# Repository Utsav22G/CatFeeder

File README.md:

# CatFeeder
Final Project for Real World Microcontrollers Fall 2020 - Kitty Caddy cat feeder 

## Acknowledgement
Stan Reifel

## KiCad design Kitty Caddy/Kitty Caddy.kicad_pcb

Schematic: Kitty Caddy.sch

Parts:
C1: 10uF; CP_Radial_D5.0mm_P2.00mm
C2, C7, C8, C9, C10, C13, C14, C15: 0.1uF; C_0603
C3: 100uF; CP_Radial_D10.0mm_P5.00mm
C4: 47uF; CP_Radial_D10.0mm_P5.00mm
C5: 0.01uF; C_0603
C6: 220uF; CP_Radial_D12.5mm_P5.00mm
C11, C12: 22pF; C_0603
D1: B340; D_SMA
D2: RX Red; LED_0603
D3: TX Green; LED_0603
D4: D_RESET; D_SMA
D5: Debug LED; LED_0603
J1: PJ-051A; CUI_PJ-051A
J2: Motor Conn VM; Pin_Header_Straight_1x04_Pitch2.54mm
J3: Optocoupler Conn VM; Pin_Header_Straight_1x05_Pitch2.54mm
J4: Serial Conn RM; Pin_Header_Straight_1x06_Pitch2.54mm
J5: ICSP Header VM; Pin_Header_Straight_2x03_Pitch2.54mm
L1: 15uH; L_Radial_D12.0mm_P10.00mm_Neosid_SD12_style1
R1, R2, R8, R9, R12, R13, R14, R16, R17: 10k; R_0603
R3: 10k; R_0805
R4: 3.24k; R_0805
R5: 120; R_0603
R6: 22k; R_0603
R7, R10, R11, R15: 1k; R_0603
SW1: UP; SPST_ESwitch
SW2: DOWN; SPST_ESwitch
SW3: MODE; SPST_ESwitch
TP1: TP_RXL; TestPoint_Pad_D1.5mm
TP2: TP_TXL; TestPoint_Pad_D1.5mm
TP3: TP_UP1; TestPoint_Pad_D1.5mm
TP4: TP_UP2; TestPoint_Pad_D1.5mm
TP5: TP_X1; TestPoint_Pad_D1.5mm
TP6: TP_X2; TestPoint_Pad_D1.5mm
U1: OLED_Display; Pin_Header_Straight_1x04_Pitch2.54mm
U2: DRV8825
U3: TPS5430DDA; TI_SO-PowerPAD-8_ThermalVias
U4: DS3231 RTC; Pin_Header_Straight_1x08_Pitch2.54mm
U5: 74HC14D; SOIC-14_N
U6: ATmega328P-AU; TQFP-32_7x7mm_Pitch0.8mm
Y1: 16MHz; SMD-3225_4P

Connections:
+5V: C6.1, C7.1, C14.2, D4.1 (K), J4.4, J5.2, L1.2, R1.2, R2.2, R3.1, R5.1, R6.2, R8.2, R9.2, R10.1, R11.1, R12.2, R17.2, U1.2, U2.5, U2.6, U4.1, U5.14, U6.4 (VCC), U6.6 (VCC), U6.18 (AVCC)
+12V: C1.1, C2.1, C3.1, C4.1, J1.1, U2.9, U3.7 (VIN)
DIR: U2.8, U6.14 (PB2)
DOWN_BTN: U5.6, U6.11 (PD7)
DTR: C8.2, J4.1, R7.2
GND: C1.2, C2.2, C3.2, C4.2, C6.2, C7.2, C9.2, C10.2, C11.2, C12.2, C13.2, C14.1, C15.2, D1.2 (A), D5.1 (K), J1.2, J1.3, J1.5, J1.6, J3.2, J3.4, J4.5, J4.6, J5.6, R4.2, R7.1, SW1.1, SW1.2, SW2.1, SW2.2, SW3.3, SW3.4, U1.1, U2.10, U2.16, U3.6 (GND), U3.9 (GNDPAD), U4.2, U5.7, U6.3 (GND), U6.5 (GND), U6.21 (GND), Y1.2, Y1.4
M0: U2.2, U6.32 (PD2)
M1: U2.3, U6.1 (PD3)
M2: U2.4, U6.2 (PD4)
MISO: J5.1, U6.16 (PB4)
MODE_BTN: U5.12, U6.10 (PD6)
MOSI: J5.4, U6.15 (PB3)
unnamed: C5.1, D1.1 (K), L1.1, U3.8 (PH)
unnamed: C5.2, U3.1 (BOOT)
unnamed: C9.1, R13.2, TP3.1, U5.1
unnamed: C10.1, R14.2, U5.5
unnamed: C11.1, TP5.1, U6.7 (XTAL1/PB6), Y1.1
unnamed: C12.1, TP6.1, U6.8 (XTAL2/PB7), Y1.3
unnamed: C13.1, R16.1, U5.13
unnamed: C15.1, U6.20 (AREF)
unnamed: D2.2 (A), R10.2, TP1.1
unnamed: D3.2 (A), R11.2, TP2.1
unnamed: D5.2 (A), R15.2
unnamed: J2.1, U2.13
unnamed: J2.2, U2.14
unnamed: J2.3, U2.12
unnamed: J2.4, U2.11
unnamed: J3.1, R5.2
unnamed: R8.1, R13.1, SW1.3, SW1.4
unnamed: R9.1, R14.1, SW2.3, SW2.4
unnamed: R16.2, R17.1, SW3.1, SW3.2
RESET_PIN: C8.1, D4.2 (A), J5.5, R12.1, U6.29 (~RESET~/PC6)
RXI: D2.1 (K), J4.2, U6.31 (PD1)
SCK: J5.3, R15.1, U6.17 (PB5)
SCL: R1.1, U1.3, U4.3, U6.28 (PC5)
SDA: R2.1, U1.4, U4.4, U6.27 (PC4)
SENSE: J3.5, R6.1, U6.23 (PC0)
STEP: U2.7, U6.13 (PB1)
TXO: D3.1 (K), J4.3, U6.30 (PD0)
UP_BTN: TP4.1, U5.2, U6.9 (PD5)
V_SNS: R3.2, R4.1, U3.4 (VSENSE)

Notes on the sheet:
VIN -> 10.8 V - 19.8 V
Buck Converter
Crystal Oscillator
Motor Driver
Serial TX and RX LEDs
SCK = PIN13
Hardware Debounce for buttons using a Schmitt-trigger IC https://hackaday.com/2015/12/09/embed-with-elliot-debounce-your-noisy-buttons-part-i/
Optocoupler
LED _AN = 1
Power Flags
User Input Buttons
Phototransistor Design Guide https://www.onsemi.com/pub/Collateral/AN-3005-D.PDF
Orange
Green
Blue
White
LED_CAT = 2
BJT_EMTR = 5
BJT_CLCTR = 4
Modules
I2C Pullup
Reset Pins

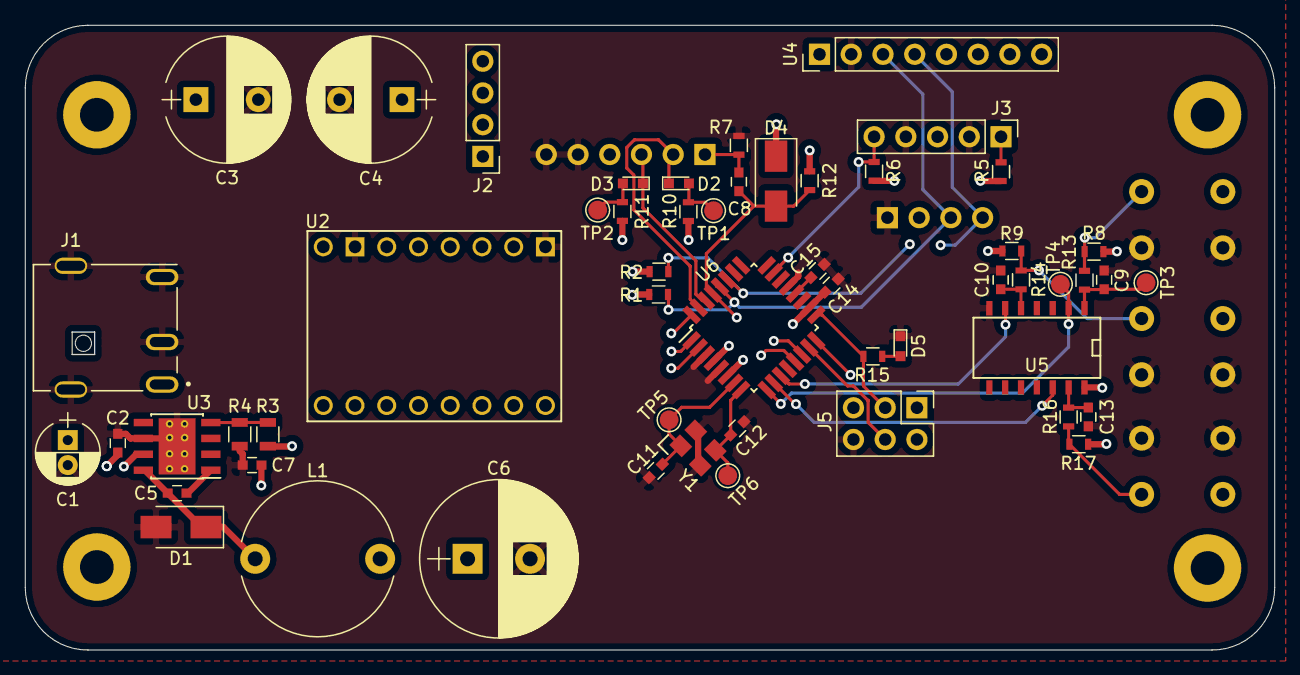
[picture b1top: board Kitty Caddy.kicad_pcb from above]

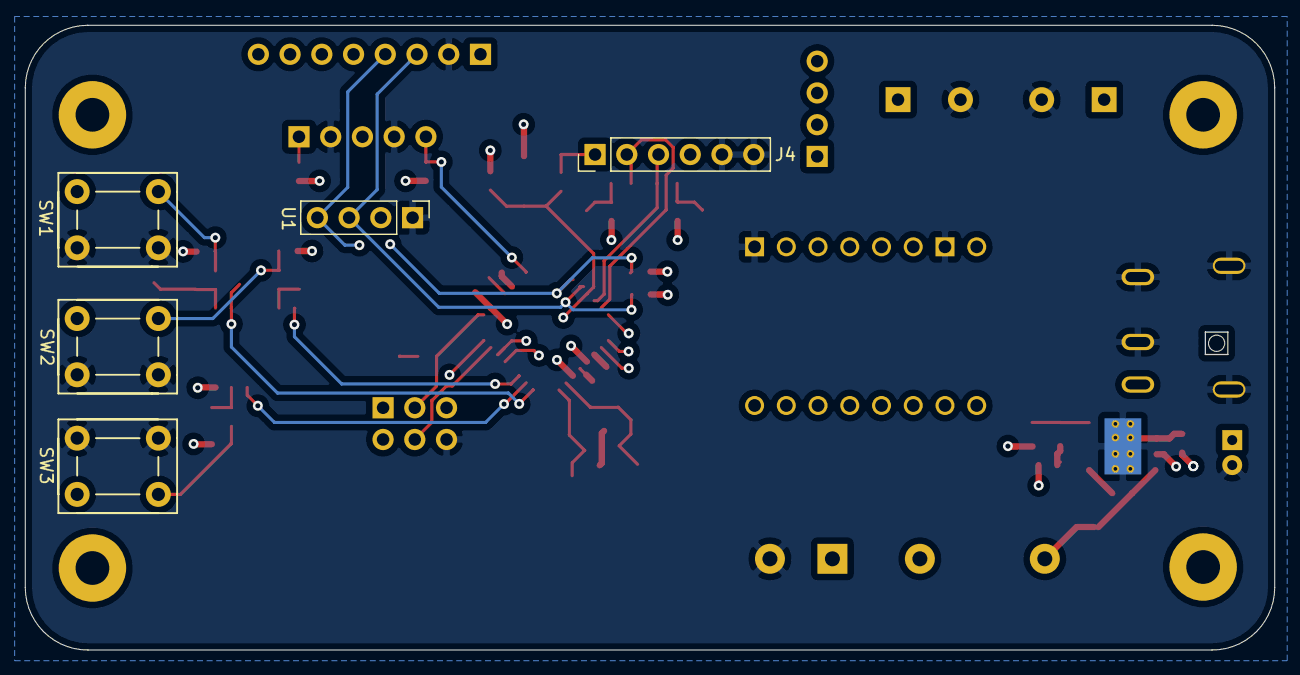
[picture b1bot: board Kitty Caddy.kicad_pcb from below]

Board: 4 copper layers, 100.0 x 50.0 mm, 59 parts (5 on the bottom side), 41 nets.

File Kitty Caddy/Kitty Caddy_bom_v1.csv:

Component,Description,Part,References,Value,Footprint,Quantity Per PCB,Datasheet,Vendor,Vendor Part #,Manufacturer,Link,Comments
1,Unpolarized capacitor,C,C5,0.01uF,C_0603,1,~,,,,,
2,Unpolarized capacitor,C,C2 C7 C8 C9 C10 C13 C14 C15,0.1uF,C_0603,8,~,,,,,
3,Polarized capacitor,CP,C3,100uF,CP_Radial_D10.0mm_P5.00mm,1,https://www.nichicon.co.jp/english/products/pdfs/e-ukl.pdf,DigiKey,493-13402-ND,Nichicon,,
4,Polarized capacitor,CP,C1,10uF,CP_Radial_D5.0mm_P2.00mm,1,https://www.nichicon.co.jp/english/products/pdfs/e-ukl.pdf,DigiKey,UKL1H100KDDANA-ND,Nichicon,,
5,Polarized capacitor,CP,C6,220uF,CP_Radial_D12.5mm_P5.00mm,1,https://www.nichicon.co.jp/english/products/pdfs/e-ukl.pdf,DigiKey,493-14487-ND,Nichicon,,
6,"Unpolarized capacitor, small symbol",C_Small,C11 C12,22pF,C_0603,2,~,LCSC,C1653,Samsung Electro-Mechanics,,
7,Polarized capacitor,CP,C4,47uF,CP_Radial_D10.0mm_P5.00mm,1,https://www.nichicon.co.jp/english/products/pdfs/e-ukl.pdf,DigiKey,493-13402-ND,Nichicon,,
8,"20V 3A Schottky Barrier Rectifier Diode, SMC",B340,D1,B340,D_SMA,1,1903051003_MDD-Jiangsu-Yutai-Elec-SS14_C2480.pdf,LCSC,C2480,Microdiode Electronics,,
9,Diode,D,D4,D_RESET,D_SMA,1,https://datasheet.lcsc.com/szlcsc/MDD-Jiangsu-Yutai-Elec-M7-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,LCSC,C95872,Microdiode Electronics,,
10,Light emitting diode,LED,D5,Debug LED,LED_0603,1,Everlight-Elec-19-217-BHC-ZL1M2RY-3T_C72041.pdf,LCSC,C72041,Everlight Elec,,
11,Light emitting diode,LED,D2,RX Red,LED_0805,1,Foshan-NationStar-Optoelectronics-FC-2012HRK-620D_C84256.pdf,LCSC,C84256,Foshan NationStar Optoelectronics,,
12,Light emitting diode,LED,D3,TX Green,LED_0603,1,Everlight-Elec-19-217-GHC-YR1S2-3T_C72043.pdf,LCSC,C72043,Everlight Elec,,
13,"Generic connector, double row, 02x03, odd/even pin numbering scheme (row 1 odd numbers, row 2 even numbers), script generated (kicad-library-utils/schlib/autogen/connector/)",Conn_02x03_Odd_Even,J5,ICSP Header VM,Pin_Header_Straight_2x03_Pitch2.54mm,1,~,DigiKey,1849-PR20203VBDN-ND,METZ CONNECT USA Inc.,,
14,"Generic connector, single row, 01x04, script generated (kicad-library-utils/schlib/autogen/connector/)",Conn_01x04,J2,Motor Conn VM,Pin_Header_Straight_1x04_Pitch2.54mm,1,~,DigiKey,WM2702-ND,Molex,,
15,"Generic connector, single row, 01x05, script generated (kicad-library-utils/schlib/autogen/connector/)",Conn_01x05,J3,Optocoupler Conn VM,Pin_Header_Straight_1x05_Pitch2.54mm,1,~,DigiKey,WM2703-ND,Molex,,
16,"DC Power Jack Conn 2.0 mm Center Pin, 2.5 A, Right Angle, Through Hole, Shielded",PJ-051A,J1,PJ-051A,CUI_PJ-051A,1,https://www.cuidevices.com/product/resource/pj-051a.pdf,DigiKey,CP-051A-ND,CUI Inc.,https://www.digikey.com/product-detail/en/cui-inc/PJ-051A/CP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,https://electronics.stackexchange.com/questions/2381/deciphe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
17,"Generic connector, single row, 01x06, script generated (kicad-library-utils/schlib/autogen/connector/)",Conn_01x06,J4,Serial Conn RM,Pin_Header_Straight_1x06_Pitch2.54mm,1,~,DigiKey,1849-PR20206HBNN-ND,METZ CONNECT USA Inc.,,
18,Inductor,L,L1,15uH,L_Radial_D12.0mm_P10.00mm_Neosid_SD12_style1,1,https://www.we-online.de/katalog/datasheet/744750460150.pdf,DigiKey,732-10828-ND,Würth Elektronik,,
19,Resistor,R,R8 R9 R12 R13 R14 R16 R17,10k,R_0603,7,~,,,,,
20,Resistor,R,R3,10k,R_0805,1,~,,,,,
21,Resistor,R,R5,120,R_0603,1,~,,,,,
22,Resistor,R,R7 R10 R11 R15,1k,R_0603,4,~,,,,,
23,Resistor,R,R6,22k,R_0603,1,~,,,,,
24,Resistor,R,R4,3.24k,R_0805,1,~,,,,,
25,Resistor,R,R1 R2,4k7,R_0603,2,~,,,,,
26,"Push button switch, generic, two pins",SW_Push,SW2,DOWN,SPST_TE,1,https://www.te.com/commerce/DocumentDelivery/DDEController?A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,Digikey,450-1650-ND,TE Connectivity,,
27,"Push button switch, generic, two pins",SW_Push,SW3,MODE,SPST_TE,1,https://www.te.com/commerce/DocumentDelivery/DDEController?A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,Digikey,450-1650-ND,TE Connectivity,,
28,"Push button switch, generic, two pins",SW_Push,SW1,UP,SPST_TE,1,https://www.te.com/commerce/DocumentDelivery/DDEController?A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,Digikey,450-1650-ND,TE Connectivity,,
29,Hex Inverter Scmitt-Trigger,74HC14D,U5,74HC14D,SOIC-14_N,1,https://datasheet.lcsc.com/szlcsc/Nexperia-74HC14D-653_C5605.pdf,LCSC,C5605,Nexperia,,
30,"10MHz, 4kB Flash, 512B SRAM, 256B EEPROM, TQFP-32",ATmega328P-AU,U6,ATmega328P-AU,TQFP-32_7x7mm_P0.8mm,1,http://ww1.microchip.com/downloads/en/DeviceDoc/ATmega328_P%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,LCSC,C14877,Microchip Tech,,
31,Stepper Motor Driver 8.2V to 45V 2.5A,DRV8825,U2,DRV8825,DRV8825,1,https://www.pololu.com/product-info-merged/2133,Pololu,2133,Pololu,https://www.pololu.com/product/2133,
32,RTC Breakout 5V 32KHz I2C,DS3231_Breakout,U4,DS3231 RTC,Pin_Header_Straight_1x08_Pitch2.54mm,1,https://cdn-shop.adafruit.com/product-files/3013/DS3231.pdf,Adafruit,3013,Adafruit,,
33,"0.96"" OLED 5V I2C 128x64",OLED_Display,U1,OLED_Display,Pin_Header_Straight_1x04_Pitch2.54mm,1,https://www.uctronics.com/download/Amazon/U602602.pdf,Amazon,B072Q2X2LL,Uctronics,,
34,"3A, Step Down Swift Converter, Adjustable Output Voltage, 5.5-36V Input Voltage, PowerSO-8",TPS5430DDA,U3,TPS5430DDA,TI_SO-PowerPAD-8_ThermalVias,1,http://www.ti.com/lit/ds/symlink/tps5430.pdf,LCSC,C9864,Texas Instruments,,
35,"Four pin crystal, GND on pins 2 and 4",Crystal_GND24,Y1,16MHz,SMD-3225_4P,1,https://datasheet.lcsc.com/szlcsc/Yangxing-Tech-X322516MLB4S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,LCSC,C13738,Yangxing Tech,,





Component Groups:,35
Component Count:,53
Fitted Components:,53
Number of PCBs:,1
Total components:,53
Schematic Version:,v1
Schematic Date:,2020-10-05
BoM Date:,10/26/2020 7:07:13 PM
Schematic Source:,C:\Users\ugupta\Desktop\Fall 2020\Microcontrollers\Kitty Caddy\Kitty Caddy.sch
KiCad Version:,Eeschema (5.1.6)-1

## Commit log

2020-11-04 Adding project files
